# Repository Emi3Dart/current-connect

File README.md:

# current-connect
Proyecto y Diseño Electrónico

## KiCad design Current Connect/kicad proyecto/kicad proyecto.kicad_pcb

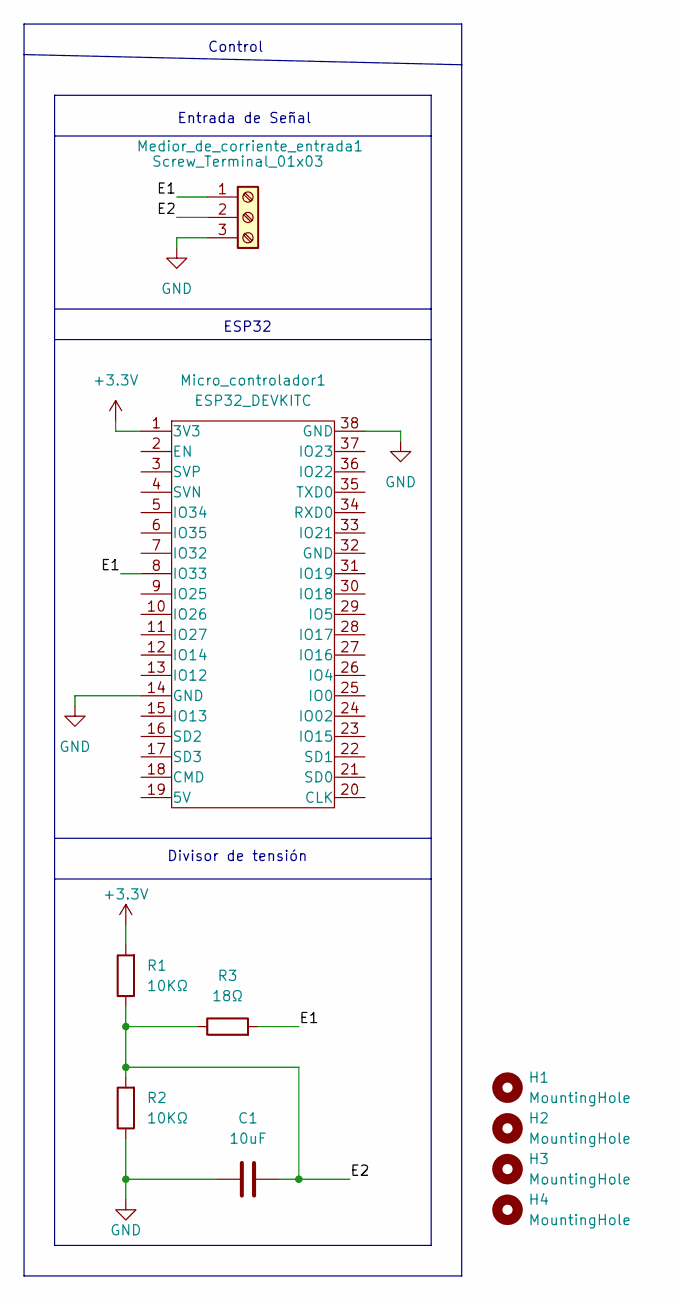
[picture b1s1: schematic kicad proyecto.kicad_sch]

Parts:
C1: 10uF; CAP_ELEC_8x11.5mm
H1, H2, H3, H4: MountingHole; Separador_M3_5mm
Medior_de_corriente_entrada1: Screw_Terminal_01x03; TerminalBlock_bornier-3_P5.08mm
Micro_controlador1: ESP32_DEVKITC
R1, R2: 10KΩ; RES0.3
R3: 18Ω; RES0.3

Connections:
+3V3: Micro_controlador1.1 (3V3), R1.2
/E1: Medior_de_corriente_entrada1.1, Micro_controlador1.8 (IO33), R3.2
/E2: C1.2, Medior_de_corriente_entrada1.2, R1.1, R2.2, R3.1
GND: C1.1, Medior_de_corriente_entrada1.3, Micro_controlador1.14 (GND), Micro_controlador1.38 (GND), R2.1

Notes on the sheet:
ESP32
Control
Divisor de tensión
Entrada de Señal

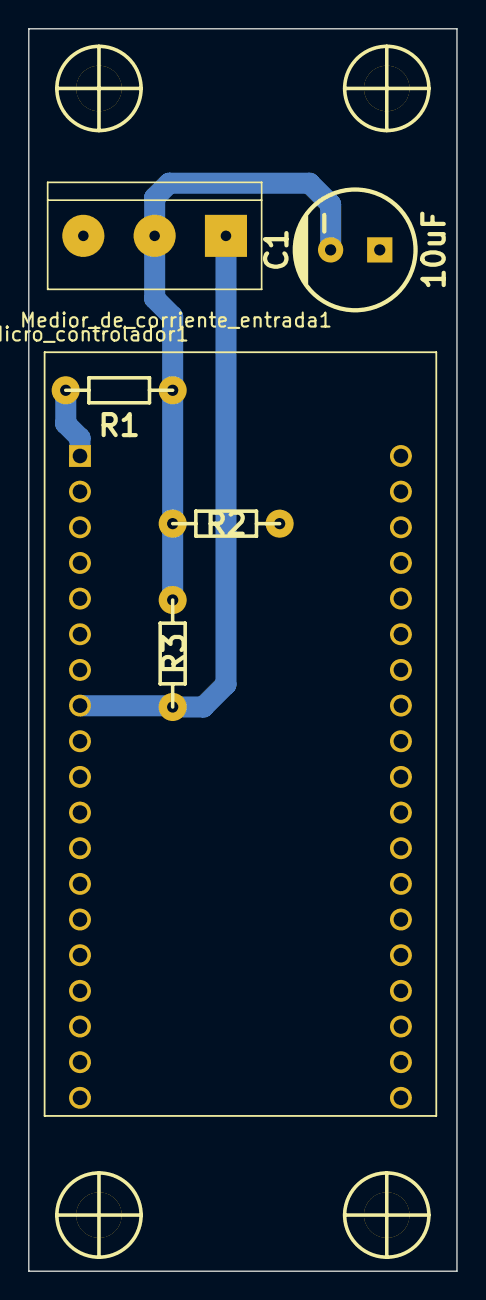
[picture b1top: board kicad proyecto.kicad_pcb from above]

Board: 2 copper layers, 30.5 x 88.5 mm, 10 parts (0 on the bottom side), 4 nets.

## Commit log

2022-08-22 current connect
